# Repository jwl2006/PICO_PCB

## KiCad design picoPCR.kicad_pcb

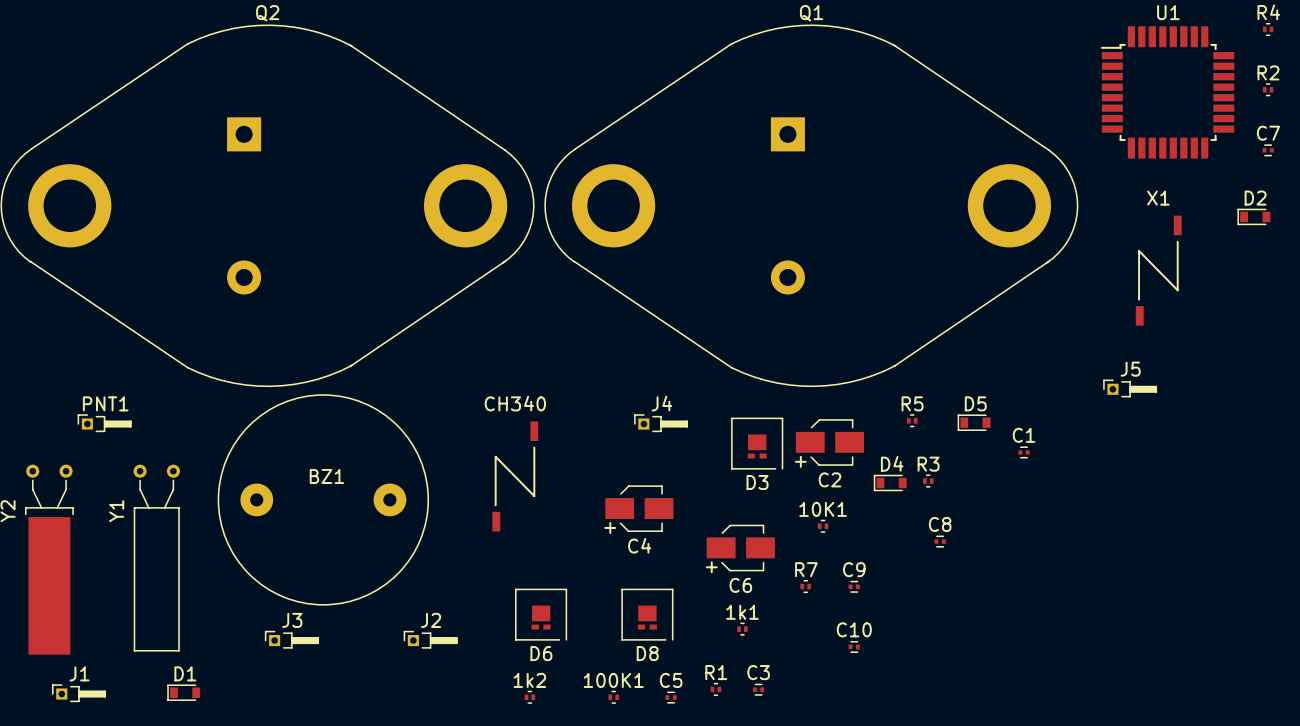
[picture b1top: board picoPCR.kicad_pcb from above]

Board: 2 copper layers, 41 parts (0 on the bottom side), 27 nets, no tracks yet.

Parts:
1k1, 1k2, 10K1, 100K1: R_Small; R_0201
BZ1: Buzzer; BUZZER
C1, C3, C8, C9, C10: 100n; C_0201
C2: 10u; CP_Elec_3x5.3
C4, C6: CP; CP_Elec_3x5.3
C5, C7: C; C_0201
CH340: CH340(SOP-16); Neosid_Air-Coil_SML_1turn_HDM0131A
D1, D2, D4, D5: D; D_0603
D3: POW; LED-L1T2_LUMILEDS
D6, D8: LED_Small; LED-L1T2_LUMILEDS
J1: Conn_OLED_Male; Pin_Header_Angled_1x01_Pitch1.00mm
J2: Conn_OLED; Pin_Header_Angled_1x01_Pitch1.00mm
J3: Conn_thermistor; Pin_Header_Angled_1x01_Pitch1.00mm
J4: Conn_heater; Pin_Header_Angled_1x01_Pitch1.00mm
J5: Conn_fan; Pin_Header_Angled_1x01_Pitch1.00mm
PNT1: Conn_thermistor_Male; Pin_Header_Angled_1x01_Pitch1.00mm
Q1, Q2: 2N3055; TO-3
R1, R2, R3, R4: 1K; R_0201
R5: R_Small; R_0201
R7: 100; R_0201
U1: ATMEGA328P-AU; TQFP-32_7x7mm_Pitch0.8mm
X1: micro-usb-ab; Neosid_Air-Coil_SML_1turn_HDM0131A
Y1: 12MHz; Crystal_AT310_d3.0mm_l10.0mm_Horizontal
Y2: 16MHz; Crystal_AT310_d3.0mm_l10.0mm_Horizontal_1EP_style1

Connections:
GNDD: 100K1.1, BZ1.2, C1.1, C2.2, C3.2, C8.2, C10.2, CH340.1, D3.1, D4.1, D5.1, U1.3, U1.5, U1.21, Y1.2, Y2.2
unnamed: 1k1.1, Q1.1
unnamed: 1k1.2, U1.2
unnamed: 1k2.1, Q2.1
unnamed: 1k2.2, U1.9
unnamed: 10K1.1, C1.2, C2.1, D1.2, D2.2, D3.2, R3.1, R4.1, U1.4, U1.6, U1.18
unnamed: 10K1.2, C9.2
unnamed: 100K1.2, PNT1.1, U1.19
unnamed: BZ1.1, R7.2
unnamed: C3.1, Y1.1
unnamed: C4.1, C5.1, D1.1
unnamed: C4.2, C5.2, Q1.2
unnamed: C6.1, C7.1, D2.1
unnamed: C6.2, C7.2, Q2.2
unnamed: C10.1, U1.20
unnamed: CH340.2, R2.2
unnamed: D4.2, Q1.3
unnamed: D5.2, Q2.3
unnamed: D6.1, R2.1, U1.31
unnamed: D6.2, R3.2
unnamed: D8.1, R1.1, U1.30
unnamed: D8.2, R4.2
unnamed: J1.1, U1.27
unnamed: R5.2, U1.32
unnamed: R7.1, U1.26
unnamed: U1.7, Y2.3
unnamed: U1.8, Y2.1
